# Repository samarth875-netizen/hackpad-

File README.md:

# hackpad
This is a hackpad I created. It includes three keys, a rotary knob, and a small OLED screen. I have not added any code for it because I am making it customizable so that a person can write code for it by himself. for specifically his purposes 

 This pad was created using the xiao Seed Studio Zao and with the help of three mechanical keys, one rotary encoder, and one OLED screen. This is a basic, micro pad I created as my first PCB project.

I have edited the PCB files and the CAD files. In the repository, the CAD files include the bottom case and the upper lid, and they can be screwed together using 3 mm screws. I have not added threads, as you can directly screw the screw into the holes, and that's all.

I have attached a screenshot which includes the position of each button so that you can code by yourself. And I have not used diodes, as the seed zao doesn't need diodes until I am using a matrix. I have not used a matrix, as I have only used three keys, so I have not used a diode. 
# some photos

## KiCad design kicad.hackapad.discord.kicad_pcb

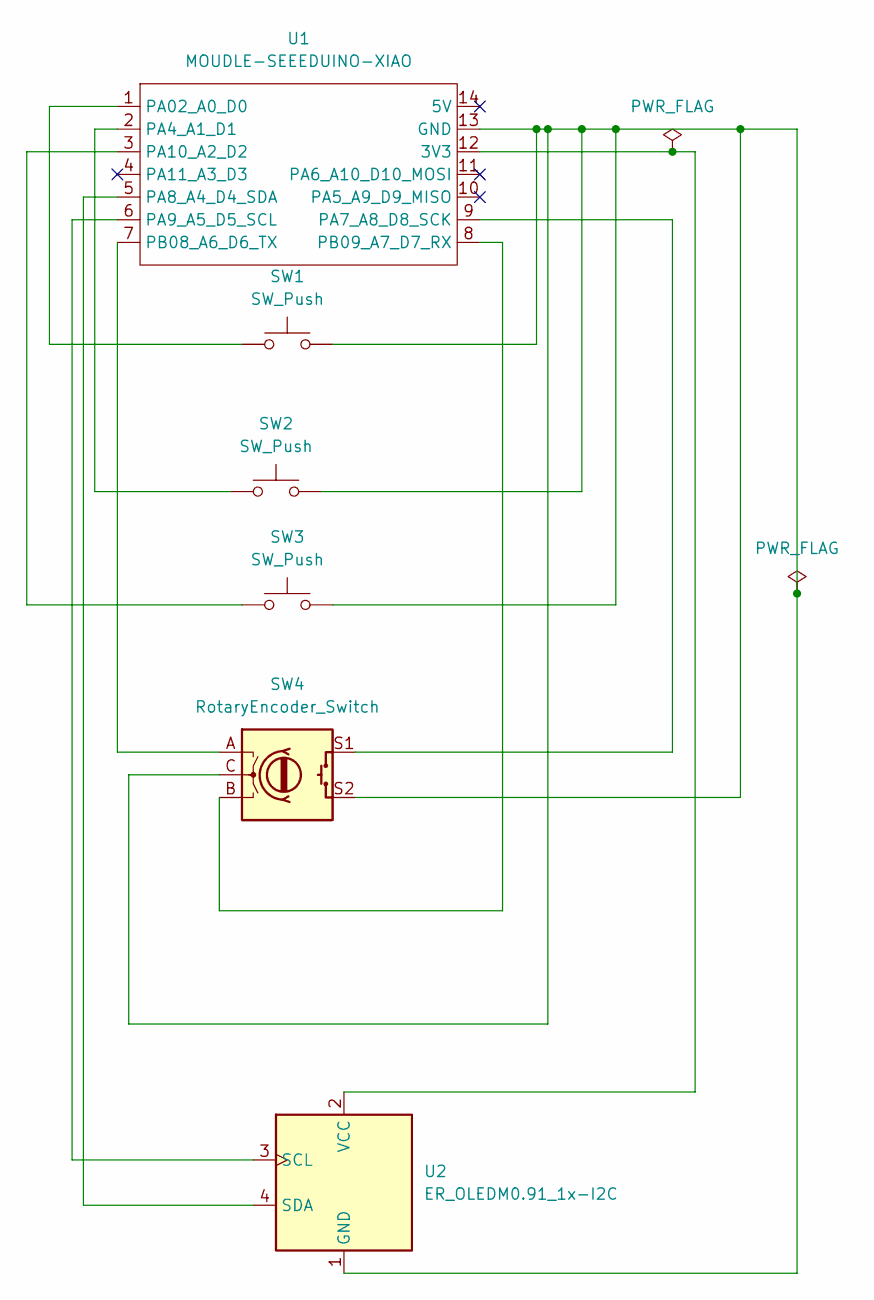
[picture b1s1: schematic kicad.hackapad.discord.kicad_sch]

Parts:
SW1, SW2, SW3: SW_Push; SW_Cherry_MX_1.00u_PCB
SW4: RotaryEncoder_Switch; RotaryEncoder_Alps_EC11E-Switch_Vertical_H20mm
U1: MOUDLE-SEEEDUINO-XIAO; XIAO-Generic-Hybrid-14P-2.54-21X17.8MM
U2: ER_OLEDM0.91_1x-I2C

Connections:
unnamed: U1.12 (3V3), U2.2 (VCC)
unnamed: SW1.2, SW2.2, SW3.2, SW4.C, SW4.S2, U1.13 (GND), U2.1 (GND)
unnamed: SW1.1, U1.1 (PA02_A0_D0)
unnamed: SW2.1, U1.2 (PA4_A1_D1)
unnamed: SW4.S1, U1.9 (PA7_A8_D8_SCK)
unnamed: U1.5 (PA8_A4_D4_SDA), U2.4 (SDA)
unnamed: U1.6 (PA9_A5_D5_SCL), U2.3 (SCL)
unnamed: SW3.1, U1.3 (PA10_A2_D2)
unnamed: SW4.A, U1.7 (PB08_A6_D6_TX)
unnamed: SW4.B, U1.8 (PB09_A7_D7_RX)

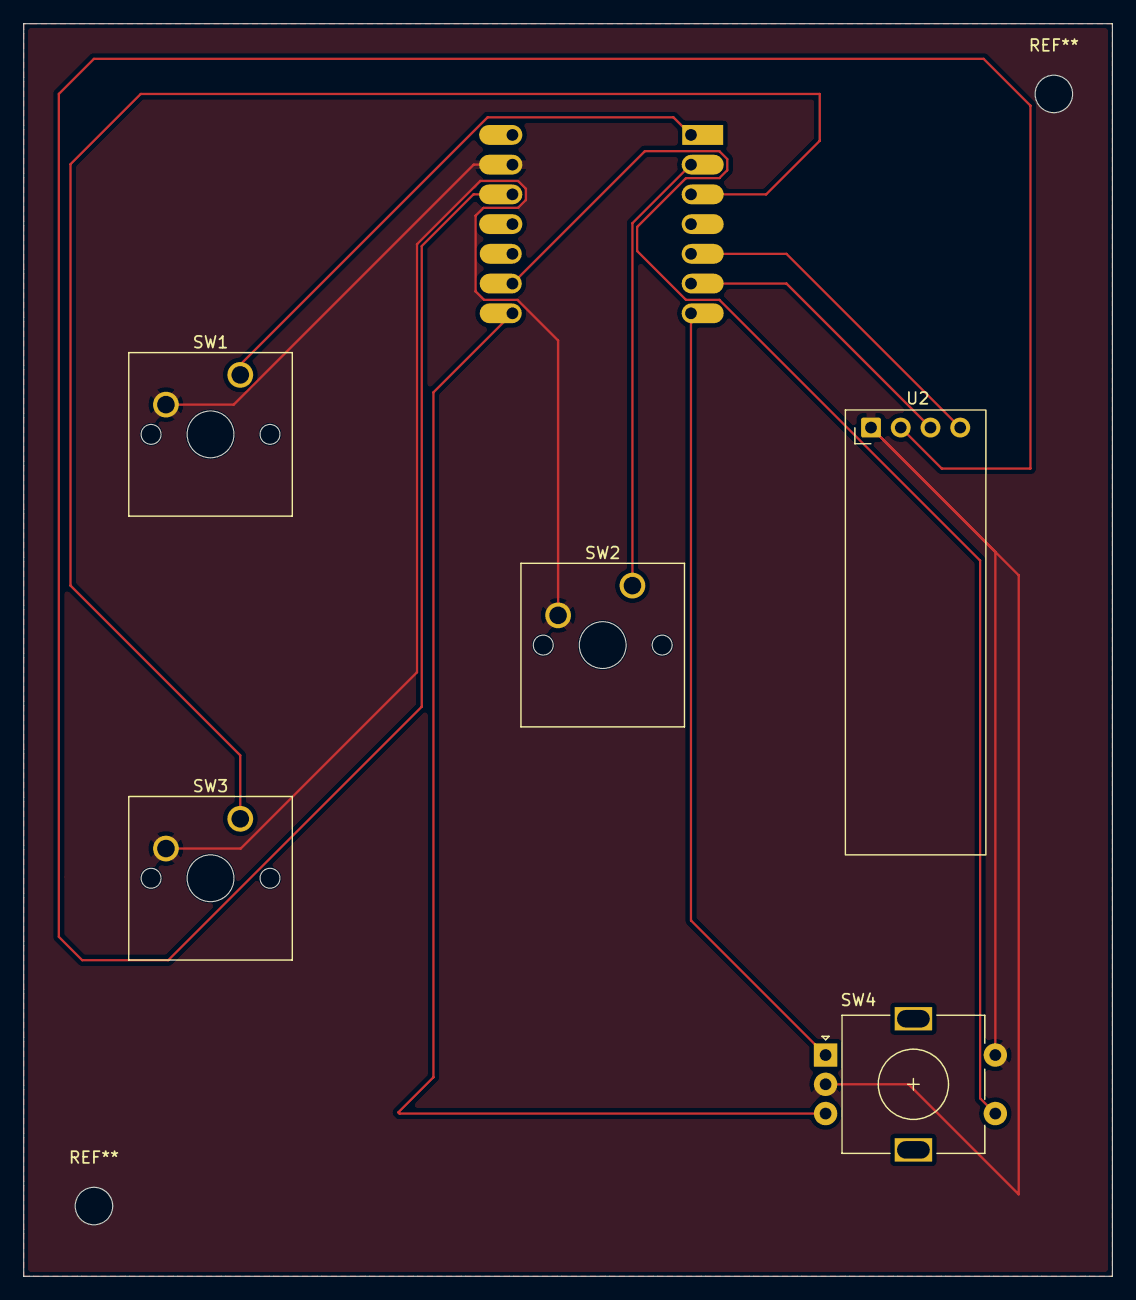
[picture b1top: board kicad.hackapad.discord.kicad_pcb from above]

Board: 2 copper layers, 93.0 x 107.0 mm, 6 parts (1 on the bottom side), 10 nets.
